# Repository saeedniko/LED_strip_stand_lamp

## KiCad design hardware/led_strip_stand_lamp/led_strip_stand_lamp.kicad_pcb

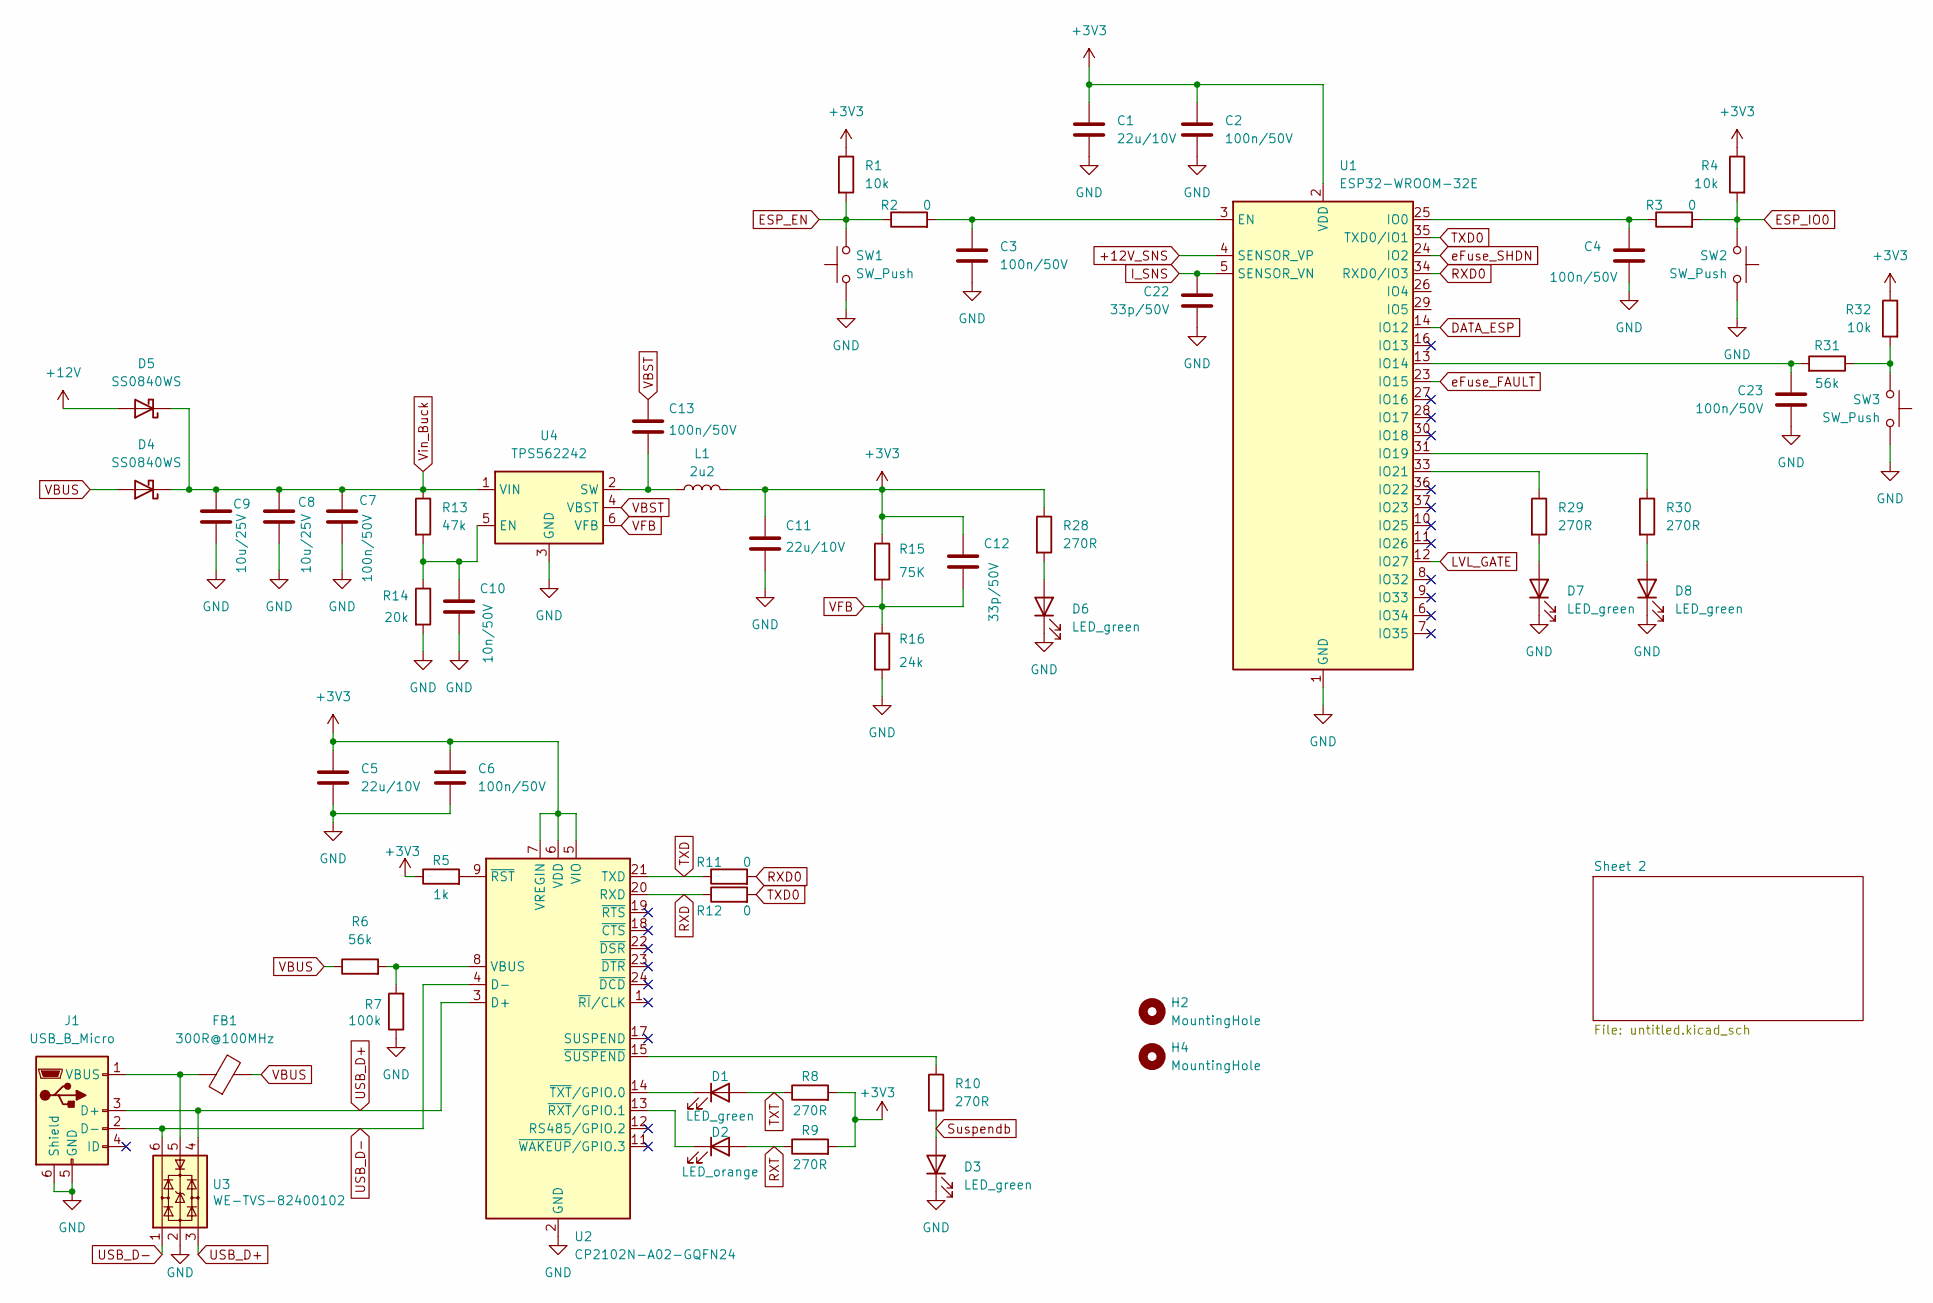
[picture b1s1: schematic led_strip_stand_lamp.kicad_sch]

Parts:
C1, C5, C11: 22u/10V; C_1206_3216Metric; MPN 81-GRM31CR71A226K15L
C2, C3, C4, C6, C7, C13, C23: 100n/50V; C_0603_1608Metric
C8, C9: 10u/25V; C_1206_3216Metric
C10: 10n/50V; C_1206_3216Metric
C12, C22: 33p/50V; C_0603_1608Metric
D1, D3, D6, D7, D8: LED_green; LED_0603_1608Metric; MPN 710-150060VS75000
D2: LED_orange; LED_0603_1608Metric; MPN 859-LTST-C190KFKT
D4, D5: SS0840WS; D_SOD-323F; MPN 241-SS0840WSR100001
FB1: 300R@100MHz; L_0603_1608Metric; MPN 710-742792641
H2, H4: MountingHole; MountingHole_3.2mm_M3
J1: USB_B_Micro; USB_Micro-B_Wuerth_629105150521; MPN 710-629105150521
L1: 2u2; L_Taiyo-Yuden_NR-24xx; MPN 963-NRH2410T2R2MN
R1, R4, R32: 10k; R_0603_1608Metric
R2, R3, R11, R12: 0; R_0603_1608Metric
R5: 1k; R_0603_1608Metric
R6, R31: 56k; R_0603_1608Metric
R7: 100k; R_0603_1608Metric
R8, R9, R10, R28, R29, R30: 270R; R_0603_1608Metric
R13: 47k; R_0603_1608Metric
R14: 20k; R_0603_1608Metric
R15: 75K; R_0603_1608Metric
R16: 24k; R_0603_1608Metric
SW1, SW2: SW_Push; SW_Push_1P1T_NO_CK_KMR2; MPN 611-KMR231NGLFS
SW3: SW_Push; SW_Tactile_SPST_Angled_PTS645Vx83-2LFS; MPN 611-PTS645VM832
U1: ESP32-WROOM-32E; ESP32-WROOM-32D
U2: CP2102N-A02-GQFN24; QFN-24-1EP_4x4mm_P0.5mm_EP2.6x2.6mm; MPN 634-CP2102NA02GQFN24
U3: WE-TVS-82400102; SOT-23-6; MPN 710-82400102
U4: TPS562242; SOT-563; MPN 595-TPS562242DRLR

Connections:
+3V3: C1.1, C2.1, C5.1, C6.1, C11.1, C12.1, L1.2, R1.1, R4.1, R5.1, R8.2, R9.2, R15.1, R28.1, R32.1, U1.2 (VDD), U2.5 (VIO), U2.6 (VDD), U2.7 (VREGIN); also elsewhere on the board
+12V: D5.2 (A); also elsewhere on the board
+12V_SNS: U1.4 (SENSOR_VP); also elsewhere on the board
DATA_ESP: U1.14 (IO12); also elsewhere on the board
ESP_EN: R1.2, R2.1, SW1.2
ESP_IO0: R3.2, R4.2, SW2.2
GND: C1.2, C2.2, C3.2, C4.2, C5.2, C6.2, C7.2, C8.2, C9.2, C10.2, C11.2, C22.2, C23.2, D3.1 (K), D6.1 (K), D7.1 (K), D8.1 (K), J1.5 (GND), J1.6 (Shield), R7.1, R14.2, R16.2, SW1.1, SW2.1, SW3.1, U1.1 (GND), U1.15 (GND), U1.38 (GND), U1.39 (GND), U2.2 (GND), U2.25 (GND), U3.2, U4.3 (GND); also elsewhere on the board
I_SNS: C22.1, U1.5 (SENSOR_VN); also elsewhere on the board
LVL_GATE: U1.12 (IO27); also elsewhere on the board
unnamed: D1.1 (K), U2.14 (~TXT/GPIO.0)
unnamed: D2.1 (K), U2.13 (~RXT/GPIO.1)
unnamed: D6.2 (A), R28.2
unnamed: D7.2 (A), R29.2
unnamed: D8.2 (A), R30.2
unnamed: FB1.1, J1.1 (VBUS), U3.5
unnamed: R31.1, R32.2, SW3.2
unnamed: C3.1, R2.2, U1.3 (EN)
unnamed: C4.1, R3.1, U1.25 (IO0)
unnamed: C23.1, R31.2, U1.13 (IO14)
unnamed: R30.1, U1.31 (IO19)
unnamed: R29.1, U1.33 (IO21)
unnamed: R6.2, R7.2, U2.8 (VBUS)
unnamed: R5.2, U2.9 (~RST)
unnamed: R10.1, U2.15 (~SUSPEND)
unnamed: C10.1, R13.2, R14.1, U4.5 (EN)
unnamed: C13.2, L1.1, U4.2 (SW)
RXD: R12.1, U2.20 (RXD)
RXD0: R11.2, U1.34 (RXD0/IO3)
RXT: D2.2 (A), R9.1
Suspendb: D3.2 (A), R10.2
TXD: R11.1, U2.21 (TXD)
TXD0: R12.2, U1.35 (TXD0/IO1)
TXT: D1.2 (A), R8.1
USB_D+: J1.3 (D+), U2.3 (D+), U3.3, U3.4
USB_D-: J1.2 (D-), U2.4 (D-), U3.1, U3.6
VBST: C13.1, U4.4 (VBST)
VBUS: D4.2 (A), FB1.2, R6.1
VFB: C12.2, R15.2, R16.1, U4.6 (VFB)
Vin_Buck: C7.1, C8.1, C9.1, D4.1 (K), D5.1 (K), R13.1, U4.1 (VIN)
eFuse_FAULT: U1.23 (IO15); also elsewhere on the board
eFuse_SHDN: U1.24 (IO2); also elsewhere on the board

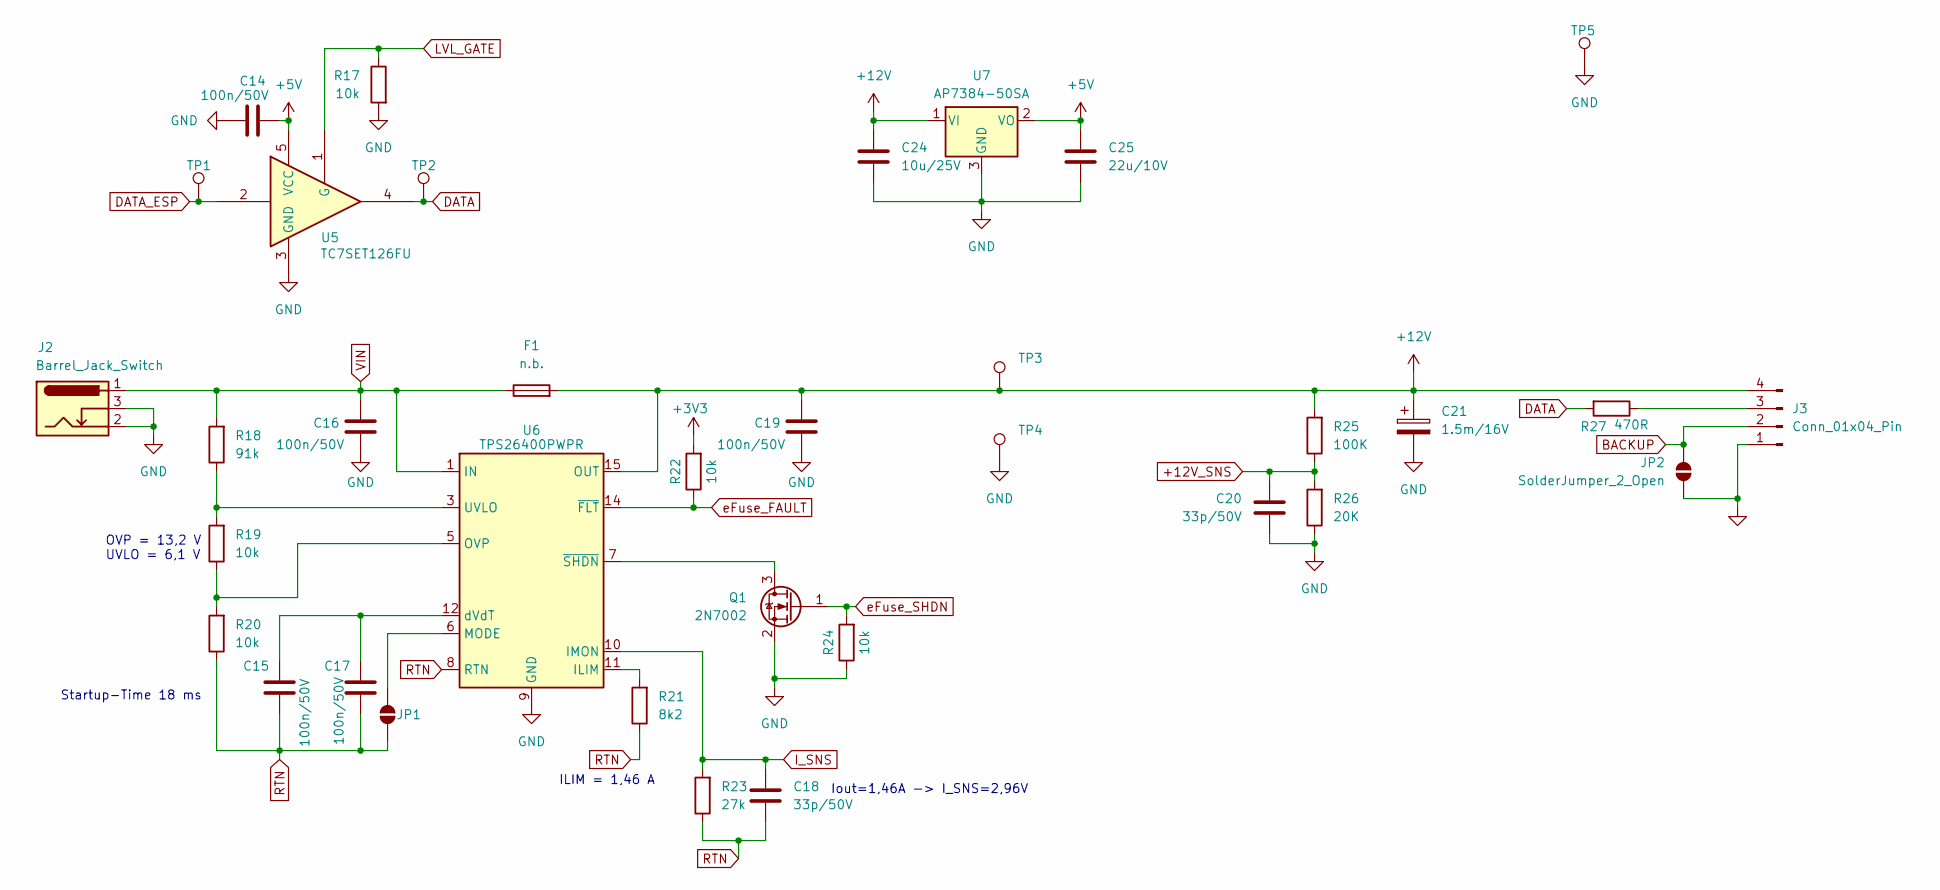
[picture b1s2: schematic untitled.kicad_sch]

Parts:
C14, C15, C16, C17, C19: 100n/50V; C_0603_1608Metric
C18, C20: 33p/50V; C_0603_1608Metric
C21: 1.5m/16V; CP_Radial_D10.0mm_P5.00mm; MPN 710-860020375019
C24: 10u/25V; C_1206_3216Metric
C25: 22u/10V; C_1206_3216Metric; MPN 81-GRM31CR71A226K15L
F1: n.b.; Fuse_1206_3216Metric; MPN 530-C1T3
J2: Barrel_Jack_Switch; BarrelJack_GCT_DCJ200-10-A_Horizontal; MPN 640-DCJ200-10-A-K1-K
J3: Conn_01x04_Pin; JST_XH_B4B-XH-A_1x04_P2.50mm_Vertical
JP1, JP2: SolderJumper_2_Open; SolderJumper-2_P1.3mm_Open_Pad1.0x1.5mm
Q1: 2N7002; SOT-23; MPN 637-2N7002
R17, R19, R20, R22, R24: 10k; R_0603_1608Metric
R18: 91k; R_0603_1608Metric
R21: 8k2; R_0603_1608Metric
R23: 27k; R_0603_1608Metric
R25: 100K; R_0603_1608Metric
R26: 20K; R_0603_1608Metric
R27: 470R; R_0603_1608Metric
TP1, TP2, TP3, TP4: TestPoint; TestPoint_Pad_D1.0mm
TP5: TestPoint; TestPoint_THTPad_D2.0mm_Drill1.0mm
U5: TC7SET126FU; SOT-353_SC-70-5; MPN 757-TC7SET126FULJCT
U6: TPS26400PWPR; HTSSOP-16-1EP_4.4x5mm_P0.65mm_EP3x3mm; MPN 595-TPS26400PWPR
U7: AP7384-50SA; SOT-23; MPN 621-AP7384-50SA-7

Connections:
+3V3: R22.2; also elsewhere on the board
+5V: C14.1, C25.1, U5.5 (VCC), U7.2 (VO)
+12V: C19.2, C21.1, C24.1, F1.2, J3.4, R25.2, TP3.1, U6.15 (OUT), U6.16 (OUT), U7.1 (VI); also elsewhere on the board
+12V_SNS: C20.1, R25.1, R26.2; also elsewhere on the board
BACKUP: J3.2, JP2.1 (A)
DATA: R27.2, TP2.1, U5.4
DATA_ESP: TP1.1, U5.2; also elsewhere on the board
GND: C14.2, C16.1, C19.1, C20.2, C21.2, C24.2, C25.2, J2.2, J2.3, J3.1, JP2.2 (B), Q1.2 (S), R17.2, R24.1, R26.1, TP4.1, TP5.1, U5.3 (GND), U6.9 (GND), U7.3 (GND); also elsewhere on the board
I_SNS: C18.1, R23.2, U6.10 (IMON); also elsewhere on the board
LVL_GATE: R17.1, U5.1 (G); also elsewhere on the board
unnamed: J3.3, R27.1
unnamed: JP1.1 (A), U6.6 (MODE)
unnamed: Q1.3 (D), U6.7 (~SHDN)
unnamed: R21.2, U6.11 (ILIM)
unnamed: R19.1, R20.2, U6.5 (OVP)
unnamed: R18.1, R19.2, U6.3 (UVLO)
unnamed: C15.2, C17.2, U6.12 (dVdT)
RTN: C15.1, C17.1, C18.2, JP1.2 (B), R20.1, R21.1, R23.1, U6.8 (RTN), U6.17 (RTN)
VIN: C16.2, F1.1, J2.1, R18.2, U6.1 (IN), U6.2 (IN)
eFuse_FAULT: R22.1, U6.14 (~FLT); also elsewhere on the board
eFuse_SHDN: Q1.1 (G), R24.2; also elsewhere on the board

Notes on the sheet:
Iout=1,46A -> I_SNS=2,96V
ILIM = 1,46 A
Startup-Time 18 ms
OVP = 13,2 V UVLO = 6,1 V

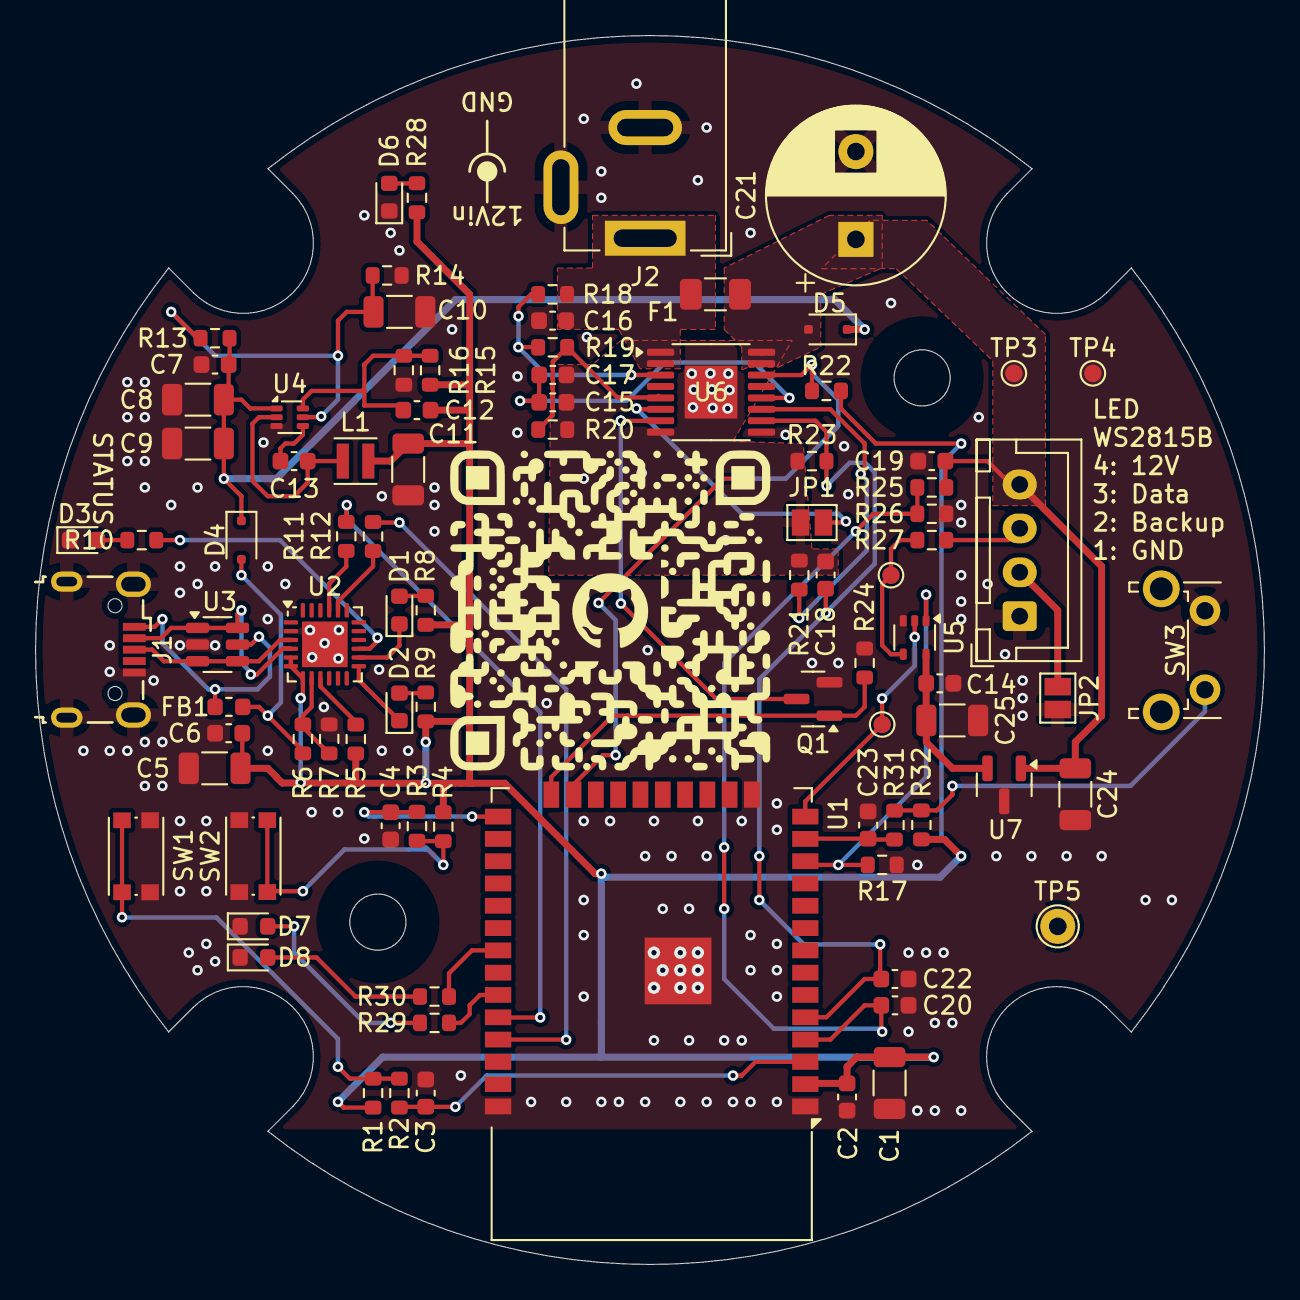
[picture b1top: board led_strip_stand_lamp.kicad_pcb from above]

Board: 2 copper layers, 70.0 x 70.0 mm, 91 parts (0 on the bottom side), 53 nets.

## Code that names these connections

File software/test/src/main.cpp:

#include <Arduino.h>
#include <FastLED.h>


#define NUM_LEDS 50
CRGB leds[NUM_LEDS];

int adcval;

// Pins
#define SCL_PIN 26
#define SDA_PIN 13
#define eFuse_SHDN 2
#define DATA_ESP 12
#define Button3 14
#define eFuse_Fault 15
#define LED_PIN1 19
#define LED_PIN2 21
#define LVL_GATE 27
#define V_SNS 36
#define I_SNS 39

void setup() {
  // Serial UART
  Serial.begin(115200);
  Serial.println("test");

  // LED library
  FastLED.addLeds<NEOPIXEL, DATA_ESP>(leds, NUM_LEDS);

  // generic gpio
  pinMode(eFuse_SHDN,OUTPUT);
  pinMode(eFuse_Fault, INPUT);
  pinMode(Button3, INPUT);
  pinMode(LED_PIN1, OUTPUT); // make led pin output mode
  pinMode(LED_PIN2, OUTPUT); // make led pin output mode
  pinMode(LVL_GATE, OUTPUT); // make led pin output mode
  pinMode(V_SNS, ANALOG);
  pinMode(I_SNS, ANALOG);

  //always high
  digitalWrite(eFuse_SHDN, 0);
  digitalWrite(LED_PIN1, 1);
  digitalWrite(LED_PIN2, 1);
  digitalWrite(LVL_GATE, 1);

}


void loop() {
for (int i = 0; i<NUM_LEDS;i++)
{
  leds[i] = CRGB::Orange; 
  FastLED.show(); 
  delay(500);
}

for (int i = (NUM_LEDS-1); i>=0;i--)
{
  leds[i] = CRGB::DarkCyan; 
  FastLED.show(); 
  delay(500);
}

adcval = analogRead(V_SNS);

Serial.print("ADC Value = ");
Serial.print(adcval);

}

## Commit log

2024-05-06 Added KiCad files
2024-05-06 first step in KiCad
2024-05-08 add USB
2024-05-09 add QR code
2024-05-27 update PCB
2024-05-30 Restructure folders in repository
2024-05-30 Update with last elements
2024-05-30 arrange the components on the board
2024-05-30 Resolve problem with 3.3V &3V3
2024-05-30 Soldering
2024-06-01 Update voltage and size
2024-06-01 Resolve problems with VIN & RTN
2024-06-03 Update thermal spoke width
2024-06-03 Review the PCB
2024-06-03 Review the GNDs
2024-06-04 Update manual library
2024-06-06 Update GND
2024-06-06 generate gerber and BOM
2024-06-09 Update Resistors & remove extra files
2024-07-02 Fix errors
2024-07-02 add PlatformIO IDE
2024-12-03 Change resistor R2 and R3 to solve problem with IO0 and EN-Pin
2025-03-30 Add new code
2025-04-20 Update LED configuration and pins
2025-09-13 End os version 1.0
2026-02-01 Add blank line for improved code readability
2026-02-01 Refactor LED strip code: reduce LED count, remove unused sensor code, and simplify setup
2026-02-01 Start with ESP32
2026-02-15 Add text for USB_Controller
